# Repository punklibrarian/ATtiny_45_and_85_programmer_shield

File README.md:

ATtiny 45 and 85 Programmer Shield - For Arduino
================================================
Copyright 2011 Design Tech Industries (DTI)

DTI email: <jameskun89@rocketmail.com>

The **ATtiny 45 and 85 Programmer Shield** is the product of a bored Saturday afternoon and using what I learnt from 
reading High-Low Tech's tutorial on programming an ATtiny 45 & 85 using an Arduino (http://hlt.media.mit.edu/?p=1229).

Features:

 * Pin compatible with Uno Arduino variants
 * ATtiny Pin 0 LED (for Blink sketch test) 
 * A 10uF capacitor between RST and GND to stop Arduino auto-resetting. 
 * Open Source; OSHW compliant
 * Design files freely available

In this repository you will find the gerber files for BatchPCB (http://batchpcb.com), along with project (.pro), board (.brd) 
and schematic (.sch) files for this shield in the 'EAGLE and 'KiCad' folders. Inside the 'EAGLE' folder you will find a folder
called 'eagleUp' which contains a 3D model of the shield in SKP format **(It also has the eagleUp files themselves which includes 
a PNG that can be used for home etching of the shield).**

**I release this design WITHOUT ANY WARRANTY. I created this for fun. Please check the design before using as I am not 
responsible if it fries something on your Arduino board.**

INSTALLATION
------------
**EAGLE**
The design is saved as an EAGLE project. EAGLE PCB design software is available from www.cadsoftusa.com 
free for non-commercial use and can be installed on Windows and Mac, with Linux support through WINE. 
To use this project download it and place the directory containing these files into the "eagle" directory 
on your computer. Then open EAGLE and navigate to Projects -> eagle -> ATtiny_45_and_85_programmer_shield.

**KiCad**
KiCad EDA Suite is an Open Source alternative to EAGLE. It is available on Windows and Linux and can be installed 
on Mac. It is available from http://kicad.sourceforge.net and works in a similar way to EAGLE. You will find project 
files for KiCad in the aptly named folder in this repository. To use this project download it and place the directory 
containing these files into a folder of your choice. Then open KiCad and navigate to File -> Open -> 
'FOLDER_OF_YOUR_CHOICE' -> ATtiny_45_and_85_programmer_shield.pro

HOW TO USE
----------
To get this to work you need to add ATtiny hardware definitions to your Arduino IDE. I use Wiring 1.0 (http://wiring.org.co/download/)
on Mac OSX Lion. I downloaded the ATtiny 45 and 85 hardware definitions from the High-Low Tech website 
(http://hlt.media.mit.edu/wp-content/uploads/2011/06/attiny45_85.zip) which I unzipped and placed the resulting folder into my sketchbook's
hardware folder (/Documents/Wiring/hardware). **You may need to create the 'hardware' folder if it doesn't already exist.**

You will also need to open the ArduinoISP (WiringISP) sketch from the examples menu and upload it to the Arduino you will be using this 
shield with. After that's done your Arduino is ready for the shield!

As an example try uploading the Blink sketch to test the shield and if it all works:

 * Open the Blink sketch from the examples menu.
 * Change the pin numbers from 13 to 0.
 * Select “ATtiny45 (w/ Arduino as ISP)” or “ATtiny85 (w/ Arduino as ISP)” from the **Tools > Board** menu (leave the serial port set to that of your Arduino board).
 *  Upload the sketch.

**You can also program ATtiny 44 & 84 chips by using jumpers between the DIP socket and the correct pins on the chip. I will include a 14 pin DIP socket 
in the next revision. You will need to get the 44 and 84 hardware definitions from here: https://github.com/damellis/attiny/tree/Arduino1 and follow 
instructions found here: http://hlt.media.mit.edu/?p=1695**

The shield has a built in LED connected to the ATtiny45/85's pin 0 for convenience.

BILL OF MATERIALS
-----------------

 * 4 x 1k 1/6 watt resistor (http://littlebirdelectronics.com/products/resistor-1k-ohm-1-6-watt-pth)
 * 1 x ATtiny 45/85 µC (http://littlebirdelectronics.com/products/avr-8-pin-20mhz-8k-4ad-attiny85)
 * 1 x 8-pin DIP socket (http://littlebirdelectronics.com/products/dip-sockets-solder-tail-8pin)
 * 1 x 10mm Blue LED (http://littlebirdelectronics.com/products/diffused-led-blue-10mm)
 * 1 x 5mm Green LED (http://littlebirdelectronics.com/products/basic-led-5mm-green)
 * 1 x 5mm Red LED (http://littlebirdelectronics.com/products/basic-led-5mm-red)
 * 1 x 5mm Yellow LED (http://littlebirdelectronics.com/products/basic-led-5mm-yellow)
 * 1 x 10uF Capacitor (http://littlebirdelectronics.com/products/electrolytic-decoupling-capacitors-10uf-25v)
 * 2 x Female Header - 1X4-pin, Straight (http://littlebirdelectronics.com/products/0100-254-mm-female-header-1x4-pin-straight)

You can also find this design on BatchPCB ready to add to your cart: http://batchpcb.com/index.php/Products/73464

DISTRIBUTION
------------
The specific terms of distribution of this project are governed by the license referenced below.

LICENSE
-------
> This work is licensed under the Creative Commons Attribution-ShareAlike License.  
> 
> To view a copy of this license, visit:
> 
>   http://creativecommons.org/licenses/by-sa/3.0/  
>   http://creativecommons.org/licenses/by-sa/3.0/legalcode
> 
> or send a letter to
> 
>   Creative Commons  
>   171 Second Street, Suite 300  
>   San Francisco  
>   California, 94105  
>   USA

The "license" folder within this repository also contains copies of the
license(s) referenced above.

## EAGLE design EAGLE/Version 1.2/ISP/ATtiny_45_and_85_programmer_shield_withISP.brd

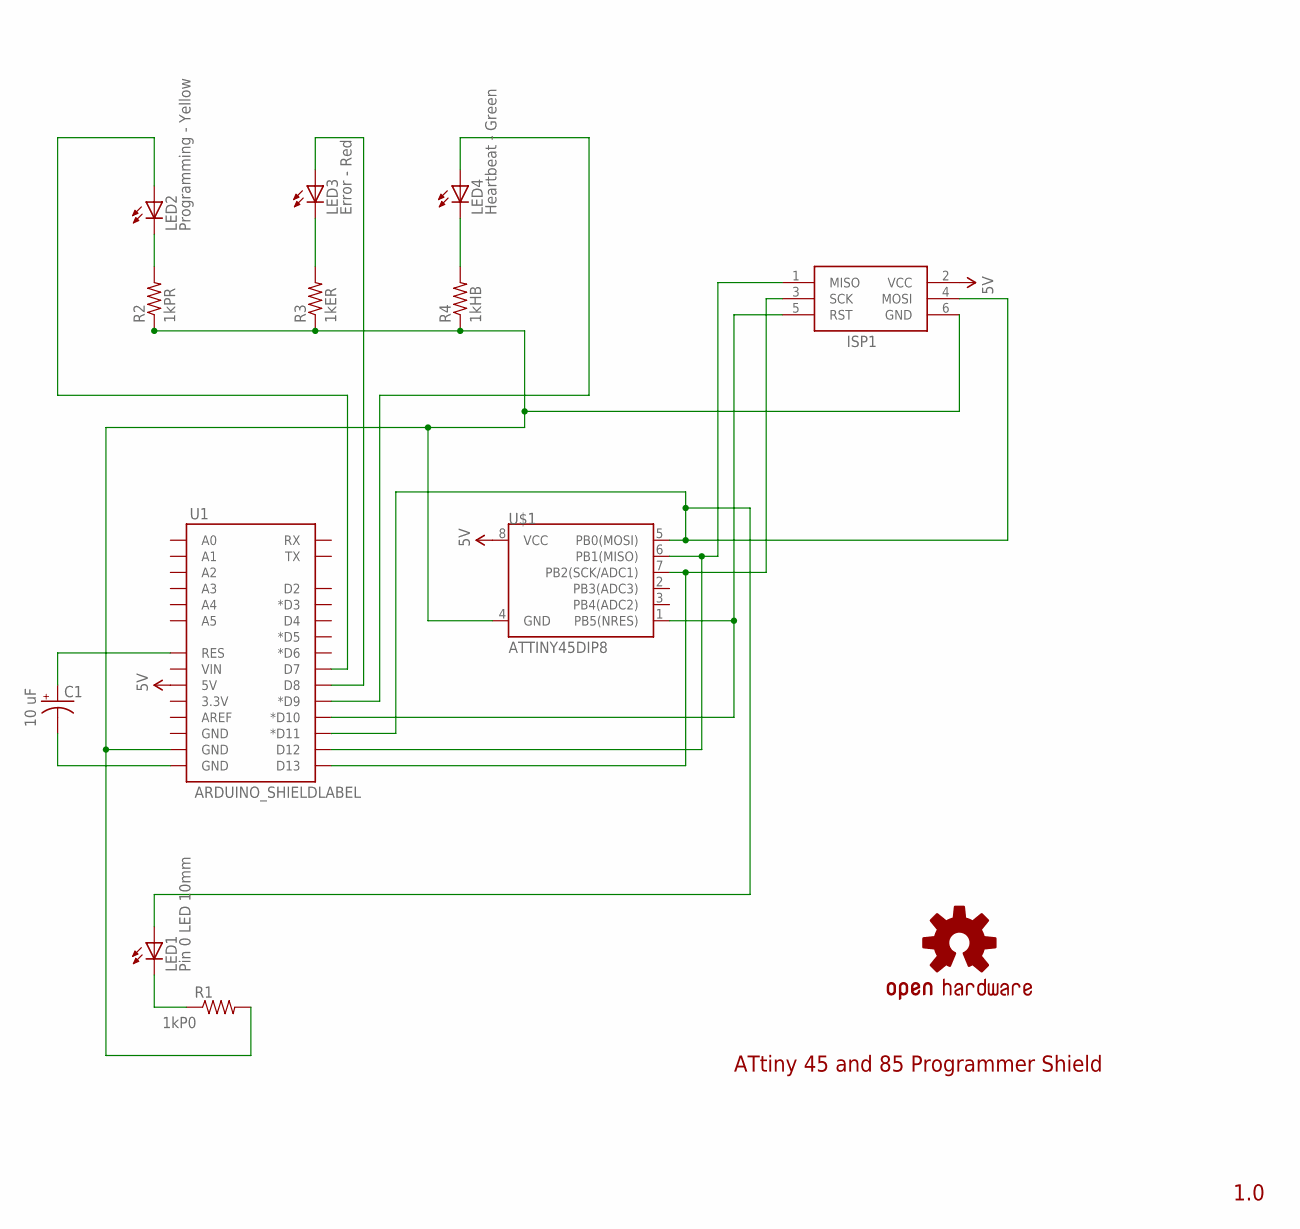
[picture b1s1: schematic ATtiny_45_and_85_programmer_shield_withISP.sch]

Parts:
C1: 10 uF; CPOL-RADIAL-10UF-25V
ISP1: AVRISP-6; AVRISP
LED1: Pin 0 LED 10mm; LED10MM
LED2: Programming - Yellow; LED5MM
LED3: Error - Red; LED5MM
LED4: Heartbeat - Green; LED5MM
R1: 1kP0; 1/6W-RES
R2: 1kPR; 1/6W-RES
R3: 1kER; 1/6W-RES
R4: 1kHB; 1/6W-RES
U1: ARDUINO_SHIELDLABEL; DUEMILANOVE_SHIELD
U$1: ATTINY45DIP8; DIP08
U$4: OSHW-LOGOL; OSHW-LOGO-L

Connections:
5V: ISP1.2 (VCC), U1.5V, U$1.8 (VCC)
unnamed: ISP1.4 (MOSI), LED1.A, U1.D11 (*D11), U$1.5 (PB0(MOSI))
unnamed: ISP1.1 (MISO), U1.D12, U$1.6 (PB1(MISO))
unnamed: ISP1.3 (SCK), U1.D13, U$1.7 (PB2(SCK/ADC1))
unnamed: C1.2 (-), U1.GND@0 (GND)
unnamed: C1.1 (+), U1.RES
unnamed: LED4.A, U1.D9 (*D9)
unnamed: LED1.C, R1.1
unnamed: LED3.A, U1.D8
unnamed: LED2.A, U1.D7
unnamed: ISP1.6 (GND), R1.2, R2.1, R3.1, R4.1, U1.GND@1 (GND), U$1.4 (GND)
unnamed: LED3.K (C), R3.2
unnamed: LED2.K (C), R2.2
unnamed: LED4.K (C), R4.2
unnamed: ISP1.5 (RST), U1.D10 (*D10), U$1.1 (PB5(NRES))

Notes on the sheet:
ATtiny 45 and 85 Programmer Shield
1.0

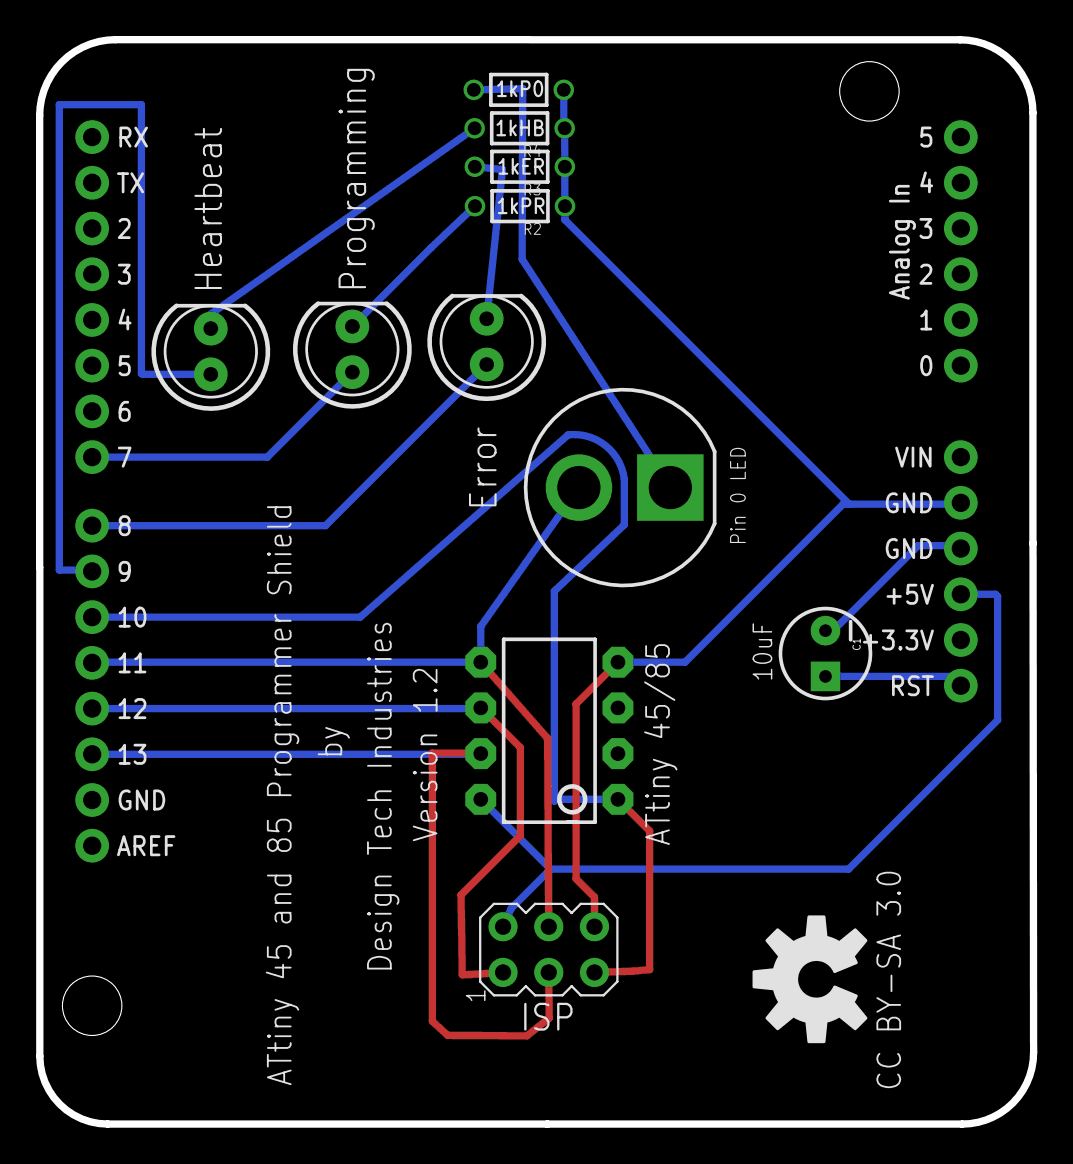
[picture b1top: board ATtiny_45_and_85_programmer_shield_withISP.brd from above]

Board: 2 copper layers, 55.2 x 60.2 mm, 13 parts (0 on the bottom side), 15 nets.

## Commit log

2011-11-26 Initial commit of README.md file.
2011-11-26 Initial commit of EAGLE design files.
2011-11-26 Initial commit of KiCad design files [KiCad files were generated by the eagle2kicad.ulp script for EAGLE]
2011-11-26 Initial commit of gerber files [for BatchPCB service]
2011-11-26 Initial commit of licence file.
2011-11-26 Initial commit of eagleUp files and 3D model of shield [without components]
2011-11-27 Created separate versions of shield [Basic is Version 1.1 and Pro is Version 1.2]
    The basic version has the programmer and test LED. The pro version has
    programming status LED's showing the action the programmer is taking,
    including an error LED.
2011-11-27 Modified Version 1.2 board after BatchPCB DRC Bot failed the files. Added board dimension to Dimension layer in EAGLE.
2011-11-28 Addition of schematic and board images of both versions.
2011-11-28 Altered Pro version to include 10mm Pin 0 LED [now allows for Yellow, Red, Green and Blue LEDs]. Added values to resistors.
2011-11-28 Changed traces and added ATtiny reset pin to Arduino pin 10 connection.
2011-11-28 Added Bill of Materials, including links to suppliers.
2011-11-28 Minor edit.
2011-11-28 Added link to BatchPCB product page.
2011-11-28 Added new images of updated board design.
2011-11-29 Added information about using version 1.2 of shield to program the ATtiny 44 and 84 µC. Edited type of capacitor used to bridge reset and ground.
2011-11-30 No change.
2011-11-30 Created new version of Pro 1.2 with ISP header.
2011-11-30 Moved gerber files to BatchPCB folder. Added gerber files for ISP version.
2011-11-30 Removed old version on gerber files.
2011-11-30 Initial commit of DorkbotPDX PCB gerber files [I believe these are the files that are needed]. Board design passed Design Rules check set by laen.
2011-12-13 Upgraded to EAGLE 6 and resaved files in new XML format.
2011-12-29 Change made to Bill of Materials.

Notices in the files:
EAGLE/Version 1.2/ISP/ATtiny_45_and_85_programmer_shield_withISP.brd:
CC BY-SA 3.0
